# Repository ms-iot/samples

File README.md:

# Windows 10 IoT Core Samples

The code in this repository has moved to [https://github.com/Microsoft/Windows-iotcore-samples](https://github.com/Microsoft/Windows-iotcore-samples).

Please use the new repository for retrieving Windows 10 IoT Core sample code and submitting your issues and pull requests.

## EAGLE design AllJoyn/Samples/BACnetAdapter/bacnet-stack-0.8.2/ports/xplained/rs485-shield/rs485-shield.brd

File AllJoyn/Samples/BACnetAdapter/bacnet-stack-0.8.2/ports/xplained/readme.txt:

BACnet MS/TP on Atmel XMEGA-A3BU XPLAINED evaluation board.

An RS-485 add-on board (daughterboard, shield) was designed
to handle the RS-485 interface and some LEDs.  See rs485-shield/
folder for EAGLE CAD design files.

Use the Configuration "Debug-XPLAINED" and not in "Debug" or "Release".
"CONF_BOARD_ENABLE_RS485_XPLAINED" is defined and used in led.c, rs485.c,
and main.c for specific board I/O. When it is not defined, the I/O is
either removed (i.e. led.c, main.c) or altered (rs485.c).

There are other defines in the "Debug-XPLAINED" Configuration
which include other parts of the XPLAINED platform code.

For your own board, you could just change rs485.c, main.c, and led.c
to use the I/O that you want to use, and not worry about the
"CONF_BOARD_ENABLE_RS485_XPLAINED". Or you can leave the
"CONF_BOARD_ENABLE_RS485_XPLAINED" in the files so that you can
always test on the XPLAINED platform with Debug-XPLAINED, and use
"Debug" or "Release" for your project.

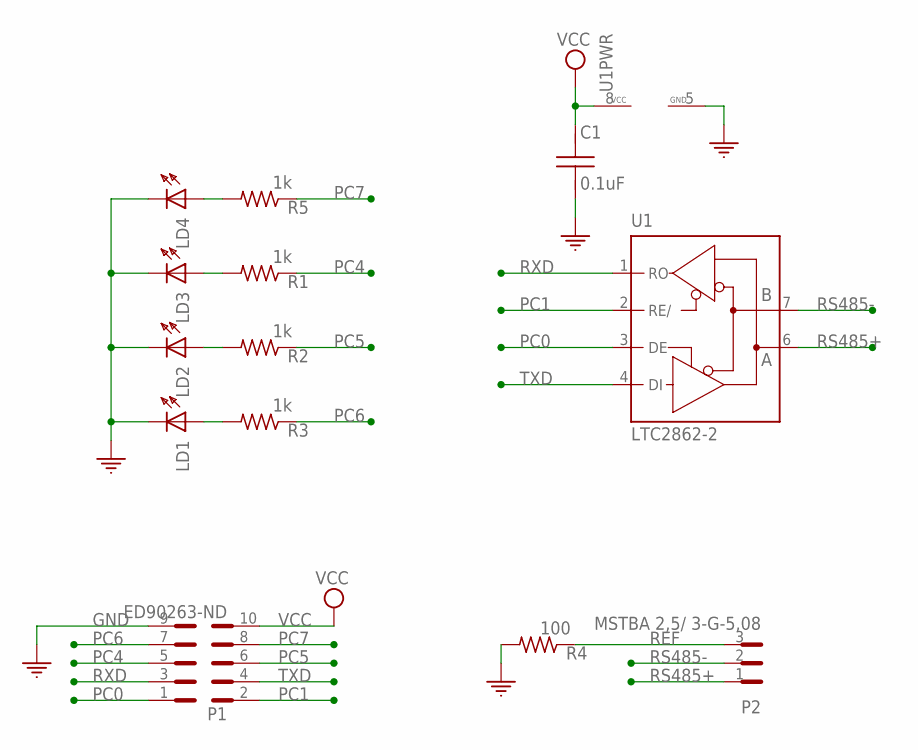
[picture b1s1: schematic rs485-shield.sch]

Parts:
C1: 0.1uF; C0805
LD1, LD2, LD3, LD4: LED-3MM
P1: ED90263-ND; PINHD2X5
P2: MSTBA 2,5/ 3-G-5,08; CON-MSTBA
R1, R2, R3, R5: 1k; RES50/500
R4: 100; RES50/500
U1: LTC2862-2; SOP08

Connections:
GND: C1.2, LD1.C, LD2.C, LD3.C, LD4.C, P1.9, R4.2, U1.5 (GND)
unnamed: LD4.A, R5.2
unnamed: LD3.A, R1.2
unnamed: LD2.A, R2.2
unnamed: LD1.A, R3.2
PC0: P1.1, U1.3 (DE)
PC1: P1.2, U1.2 (RE/)
PC4: P1.5, R1.1
PC5: P1.6, R2.1
PC6: P1.7, R3.1
PC7: P1.8, R5.1
REF: P2.3, R4.1
RS485+: P2.1, U1.6 (A)
RS485-: P2.2, U1.7 (B)
RXD: P1.3, U1.1 (RO)
TXD: P1.4, U1.4 (DI)
VCC: C1.1, P1.10, U1.8 (VCC)

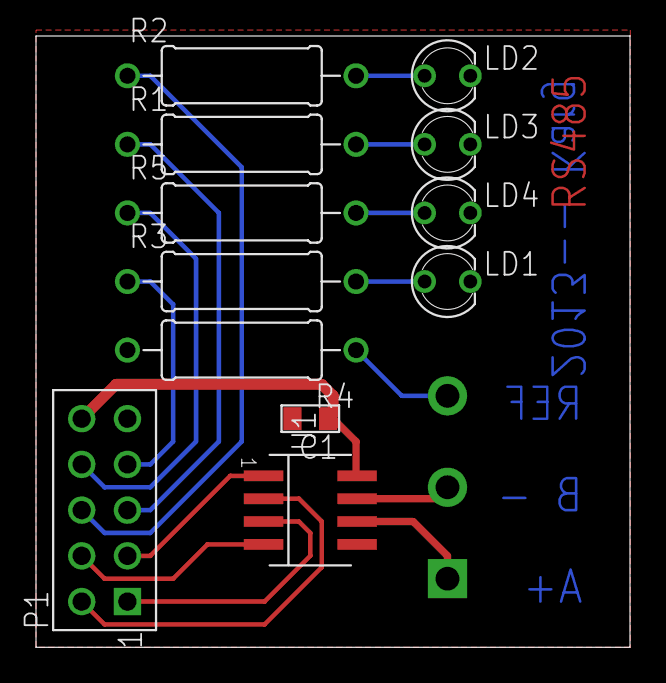
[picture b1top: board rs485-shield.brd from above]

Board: 2 copper layers, 33.0 x 34.0 mm, 13 parts (1 on the bottom side), 17 nets.

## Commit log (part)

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2016-08-16 Fix HidInjector.sln to use right architecture
2016-08-17 Checking in Plant Sensor app code sample
2016-08-18 adding binary that was ignored
2016-08-18 adding ignored binary in win32
2016-08-18 adding ignored binarys in helloblinkybackground\x64
2016-08-18 Added Copyrights and Comments
2016-08-19 Renaming back to HIDInjector
2016-08-22 User Guide
2016-08-22 Added copyright to App.xaml.cs
2016-08-23 MSFT: 8554547 This change adds passphrase conversion support on the IotOnboarding producer.
    The AllJoyn Onboarding protocol expects that the passphrase or network key is converted to a
    HEXized Ascii String (e.g. “Apple123” converts to "4170706C65313233"). On the AllJoyn Producer
    side however, the HEXized string must be converted back to a passphrase to make the WinRT call
    with the correct passphrase. This code converts the string back before onboarding the device
    to the desired network.
2016-08-24 Create IoT Templates that target Dev15
2016-08-27 Added an example for IoT Devices using the Cognitive Services API
2016-08-29 Make v14 vs v15 more consistent and easier to maintain
2016-08-30 Update version to match IoT Connector viewer
2016-08-31 Capitialised method names ChakraHost
    removed commented out unused variables
    removed email address from comments
    Changes pause from eventwait to Task.Delay().Wait()
2016-08-31 account for build server override of OutputPath
2016-08-31 fix build server paths for signing
2016-08-31 Fixing some warnings and disabling .net native compilation for IoTConnectorClient
2016-09-01 added OpenCV example program
2016-09-01 differntiate dev15 templates from dev14 templates in vsix title & description
2016-09-02 Fixed project based on code review
2016-09-08 Update license, update version
2016-09-16 Updating GpioOneWire sample to use InterruptBuffer API.
2016-09-16 Reverting to 10586 SDK version for IoT Blockly sample (#337)
2016-09-19 Change commandline to be compatible with 14393
2016-09-27 AppInstaller Bug
2016-10-07 Readding i2c, gpio and spitool test
2016-10-07 Updating readmes of test tools
2016-10-14 Update WindowsTargetPlatformVersion to new SDK version
2016-10-17 Fix for [MSRC Case 35529]: All links in IoT Connector About dialog must open in external browser
    More info here:
    https://microsoft.visualstudio.com/web/wi.aspx?pcguid=cb55739e-4afe-46a3-970f-1b49d8ee7564&id=9197777
2016-10-20 Minimize functionality in dispatcher calls (#352)
2016-10-20 Exclude all .pfx from Git
2016-10-20 Update manifest
2016-10-20 Project updates to support version 1.2.0
2016-10-20 Removed private files from commit
2016-10-22 Revert "Minimize functionality in dispatcher calls"
    This reverts commit 822e0edfa60778e65ad29734db4feb51fe2af969.
2016-10-24 enable referencing v15 tools in proj files
2016-10-24 Updated "Content-Private" to "Content"
    Fix to MS-IoT Sample template link
2016-10-26 Fixing a bug where networks with open authentication but non-open encryption
    Fixing a bug where networks with open authentication but non-open
    encryption
2016-10-27 Added NoPopUps.md
2016-10-31 Dev15 incremented v140 to v141
2016-10-31 The "Documentation for this sample" link in README.md now points to NoPopUps.md in my branch
    So I can maintain it.
    ie
    https://github.com/djaus2/samples/blob/develop/NoPopups/NoPopUps.md
2016-11-11 Bug fix - Changed HTTP links to HTTPS
2016-11-11 Incremented to version 1.3.0
2016-11-16 use VS2017 rather than Dev15
2016-11-16 fix typo in custom*.signconfig
2016-11-16 update target framework to v4.6.2 for vs2017
2016-11-17 DisplayName is too long
2016-11-17 Updating the readme
2016-11-23 Updating the Cortana launch uri for consent
2016-11-30 Modified the IotOnboarding Background Task to support the Microsoft IoT Onboarding Wifi Information Element Protocol. This change allows IoT Devices that use the Iot Onboarding application to be reco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
2016-12-01 fix vs2017 console app msvcprt paths
2016-12-01 fix binding and ap enumeration
2016-12-01 remove test strings
2016-12-01 fix build and comment on need for security
2016-12-01 add readme.md
2016-12-01 fix readme.md design numbered list
2016-12-01 protect socket access and avoid explicit ThreadPool use
2016-12-01 protect socket streams during disconnect
2016-12-05 remove express skus
2016-12-14 Update DeviceSignal.cpp
    The separation of parameter names didn't work. The code in line 234 mistakenly performed a boolean check instead of appending the ,
2016-12-17 Adding Virtual Audio Microphone Array sample driver (#384)
2016-12-17 Updated gitignore to remove VC.opendb files... (#385)
2016-12-17 Removed arm64 build, fixed issues with x86 and x64 build
2016-12-17 Removed arm64 build, fixed issues with x86 and x64 build (#386)
2016-12-20 Address Code Review
2016-12-20 Add Voice Activation, Cortana Consent and Cortana AboutMe button to IotCoreDefaultApp. (#387)
    * This change encapsulates UI changes to the IoTCoreDefaultApp for providing
    This change encapsulates UI changes to the IoTCoreDefaultApp for providingConsent and Voice Activation to Cortana. The change:
    - integrates with the latest API's available in the latest standalone SDK.
    - removes a temporary button from the BASIC settings page
    - adds a dedicated Cortana settings page to to the IotCoreDefaultApp
    - adds a "Voice Activation" toggle switch that will launch Cortana to the Consent page if Consent has not been granted
2016-12-21 Updated SDK version for Cortana Patch (#388)
    Updated SDK version for Cortana Patch
2017-01-05 Update AudioInSample to allow users to choose the render device for audio playback
2017-01-05 Add README.md for VirtualMicrophoneArrayDriver sample.
2017-01-11 Adding localized strings for IoTCoreDefaultApp
2017-01-16 Fix at upper limit of normalization bound for touch interaction.
2017-02-01 IoTCoreDefaultApp - Screen saver needs to hide cursor
2017-02-01 add more exception handling to avoid reliability issues
2017-02-02 Add NFC for IoT Sample
2017-02-02 add another null check
2017-02-04 add logic to handle exception thrown by CortanaSettings API(serve as sample for his API)
2017-02-06 Small change to one fr-fr resource. See issue # 10668645
2017-02-08 Added ability to localize "On" and "Off" strings for toggle switches. Clean up two unused variables. See issue #10668488
2017-02-11 Adding signconfig for IoT apps
2017-02-11 Update Sign Configurations for new template names
2017-02-11 Solve SignTool name collision
2017-02-14 Show error message when WiFi scanning is aborted
2017-02-14 Fixing a race condition related to the usage of DispatcherTimer()
    The problem here is that the 'timer' is created in the 'this.Loaded' handler. Notice, that the 'timer' is initialized in a low priority dispatcher context. If the user switch between pages fast enoug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
    - Scheduler invoke 'Loaded' handler
    - Handler schedules the timer-construction in a low-priority dispatcher, but not executed
    - Concurrently, the user switch away from this page
    - The scheduler invoke 'Unloaded' handler
    - Call 'timer.stop()'
2017-02-14 Fixing an unhandled exception error while scanning for WIFI networks
2017-02-15 fix Crash (file not found)
2017-02-16 Added title to sample README
2017-02-17 fix issue with reload at midnight
2017-02-21 Revert "Adding signconfig for IoT apps"
    This reverts commit 83acbb8dfd92e6e7b3b40565282fcdc2de95ec36.
2017-03-02 NotepadService must complete it's deferral
2017-03-16 Add missing Readme markdown file to IotOnboarding sample.
2017-03-20 Added Readme.md to OICAdapter sample (#425)
2017-03-20 Pushbutton sample is a better example
2017-03-21 Update for VS 2017
2017-03-22 VS2017 and package upgrade for Cognitive Services example, tested on x86 and ARM
2017-03-22 update pfx files
2017-03-23 Bulk update of samples to 15063 SDK, remove Bertha SDK build patch
2017-03-24 Clean up VideoCaptureSample code
2017-03-24 Minor code touch-ups
2017-03-27 update package family name
2017-03-29 update for ExternalProcessLauncher for VS 2017
2017-03-30 update companionapp for vs2017
2017-03-30 Fix DigitalSign sample to load user specified config file
2017-03-30 Modified Readme to point to the separately written documentation for the Home Sample Apps
    Added filter in the IoT Startup App to filter out system apps and not show them to the user
2017-03-31 release deferral
2017-03-31 Update the Speech Translator Sample (#452)
    * Add missing Readme markdown file to IotOnboarding sample.
    * Update the Speech Translator sample application to use Azure CognitiveServices.
2017-03-31 Remove AppInsights from ZigBeeAdapter
2017-03-31 Fix AllJoynVoice
2017-04-03 update companionapp for vs2017 (#449)
2017-04-04 changed the package family name reference to the new one
2017-04-04 remove ServoMotorBasics
2017-04-04 Added CustomDeviceAccessor from develop branch, changed vcxproj and pfx files for to prepare for VS2017
2017-04-05 Add ReadDeviceToCloudMessages companion to HelloCloud
2017-04-06 add readme
2017-04-06 undo sdk version change
2017-04-08 fix build
2017-04-10 build CustomDeviceAccessor in VS 2017
2017-04-11 VS 2017 build fixes
2017-04-20 add solutions that combine fb and bg in one appx
2017-04-20 change iotblockly port to 8024
2017-04-28 Fix null result and clear result list.
2017-05-12 remove BlinkyServer for node.js (HelloBlinkyBackground is identical)
2017-05-12 move samples\RaspberryCoffee to raspberry-coffee
2017-05-24 Minor text updates
2017-05-25 Updated certificates
2017-05-30 Bug: AudioInSample only works with webcams
    Update sample to be able to use all audio endpoints.
2017-06-16 fix IotCoreService build for vs2017
2017-06-20 Update HidInject.cpp
    Fix issue when injecting 2 or more keys at same time.
2017-06-22 Allow for blank password in Onboarding sample
2017-07-02 Update openZwave config
2017-07-13 Remove null conditional wait
2017-07-17 Switch from .Wait() to await
2017-07-27 update pfx to expire in 2100
2017-08-04 protect cortana calls for execution on desktop
2017-08-04 fix typo
2017-08-08 Revert change to IoTOnboardingTask.csproj
2017-08-10 Bluetooth settings bug (#511)
2017-08-24 catch NetworkAdapter exceptions if generated
2017-08-25 Updating new localized strings
2017-08-29 Incorporating Browser Page to the Default App
    a. Browser Page
    b. Connect to Browser Page on Open WiFi Network Connections
    c. TopBar User Control and applied across Pages
    d. Bluetooth BugFix
    Minor fixes
2017-08-29 Fixing Typo - Resource display
2017-08-30 Adding localized strings
2017-08-31 Browser PlaceholderText, Notification Message
    Text displays aligning to Localization Changes
2017-09-01 WindowsUpdateStatus App
    nit
2017-09-05 get dispatcher as needed rather than caching
2017-09-07 Windows update sample app
    Windows Update Sample
2017-09-12 Fix SDV DrvAckIoStop warning in gpiokmdfdemo sample (#526)
2017-09-20 protect ResetScrensaverTimeout
2017-09-20 protect ConnectToNetwork
2017-09-20 protect await calls to ConnectToNetwork*
2017-09-20 fix up some async inconsistencies
2017-09-20 share network code
2017-09-20 refactor enable/disable code
2017-10-10 update wifi connect sample
2017-10-11 Rename C# folder to CS
2017-10-19 Enabling MultiLang API calls Usage
    Marking TargetPlatform as 16278, we can change before checkin and after
    RS3 release
    Cleaned up stale Lang resource Keys
    Browser PlaceholderText, Notification Message
    Text displays aligning to Localization Changes
    MultiLang-Setting Speech-Region with Best Fit
2017-10-30 Pickup missed folder
2017-11-14 Fix misspellings
2017-12-07 Migrate samples to new repo
2018-01-02 merge
2018-04-30 Removing Python + Node
2018-11-05 make display name legal
2018-11-06 fix platform output folder
2018-11-06 try different signing parameters
2018-11-06 use in and out paths
2018-11-06 increment the version
2018-11-06 undo changes to vsixmanifest
2018-11-06 target VS from dev15 to future dev20
